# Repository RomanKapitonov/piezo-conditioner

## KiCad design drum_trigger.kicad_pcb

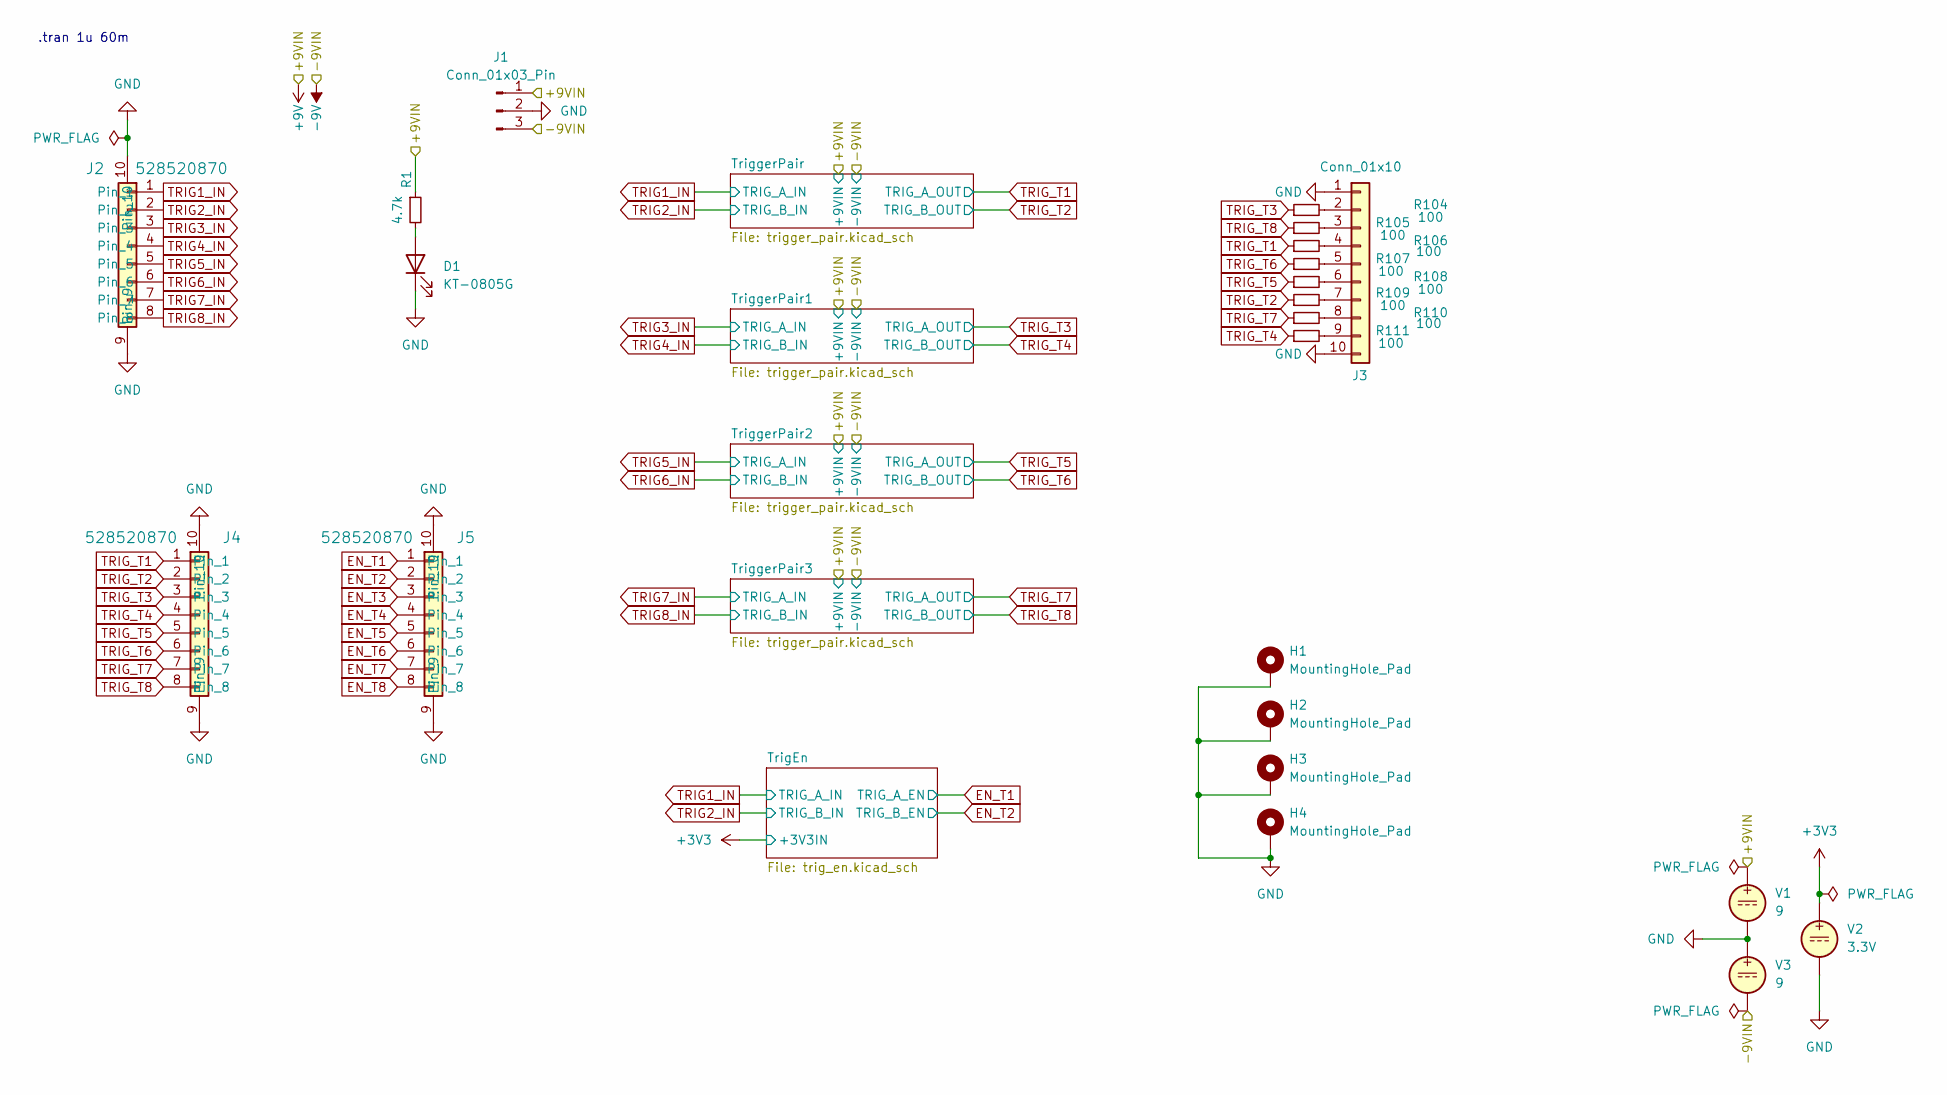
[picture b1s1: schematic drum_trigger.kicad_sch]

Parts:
D1: KT-0805G; LED_0805_2012Metric; LCSC C2297
H1, H2, H3, H4: MountingHole_Pad; MountingHole_2.2mm_M2_Pad_Via
J1: Conn_01x03_Pin; JST_PH_B3B-PH-K_1x03_P2.00mm_Vertical
J2, J4, J5: 528520870; CONN_MOLEX_528520870
J3: Conn_01x10; JST_ZH_B10B-ZR_1x10_P1.50mm_Vertical
R1: 4.7k; R_0603_1608Metric; LCSC C23162
R104, R105, R106, R107, R108, R109, R110, R111: 100; R_0402_1005Metric; LCSC C25076
V1, V3: 9
V2: 3.3V

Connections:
+9V: J1.1, R1.1, V1.1; also elsewhere on the board
-9V: J1.3, V3.2; also elsewhere on the board
GND: D1.1 (K), H1.1, H2.1, H3.1, H4.1, J1.2, J2.9, J2.10, J3.1, J3.10, J4.9, J4.10, J5.9, J5.10, V1.2, V2.2, V3.1; also elsewhere on the board
unnamed: D1.2 (A), R1.2
unnamed: J3.2, R104.2
unnamed: J3.3, R105.2
unnamed: J3.4, R106.2
unnamed: J3.5, R107.2
unnamed: J3.6, R108.2
unnamed: J3.7, R109.2
unnamed: J3.8, R110.2
unnamed: J3.9, R111.2
TRIG_T1: J4.1, R106.1; also elsewhere on the board
TRIG_T2: J4.2, R109.1; also elsewhere on the board
TRIG_T3: J4.3, R104.1; also elsewhere on the board
TRIG_T4: J4.4, R111.1; also elsewhere on the board
TRIG_T5: J4.5, R108.1; also elsewhere on the board
TRIG_T6: J4.6, R107.1; also elsewhere on the board
TRIG_T7: J4.7, R110.1; also elsewhere on the board
TRIG_T8: J4.8, R105.1; also elsewhere on the board

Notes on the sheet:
.tran 1u 60m

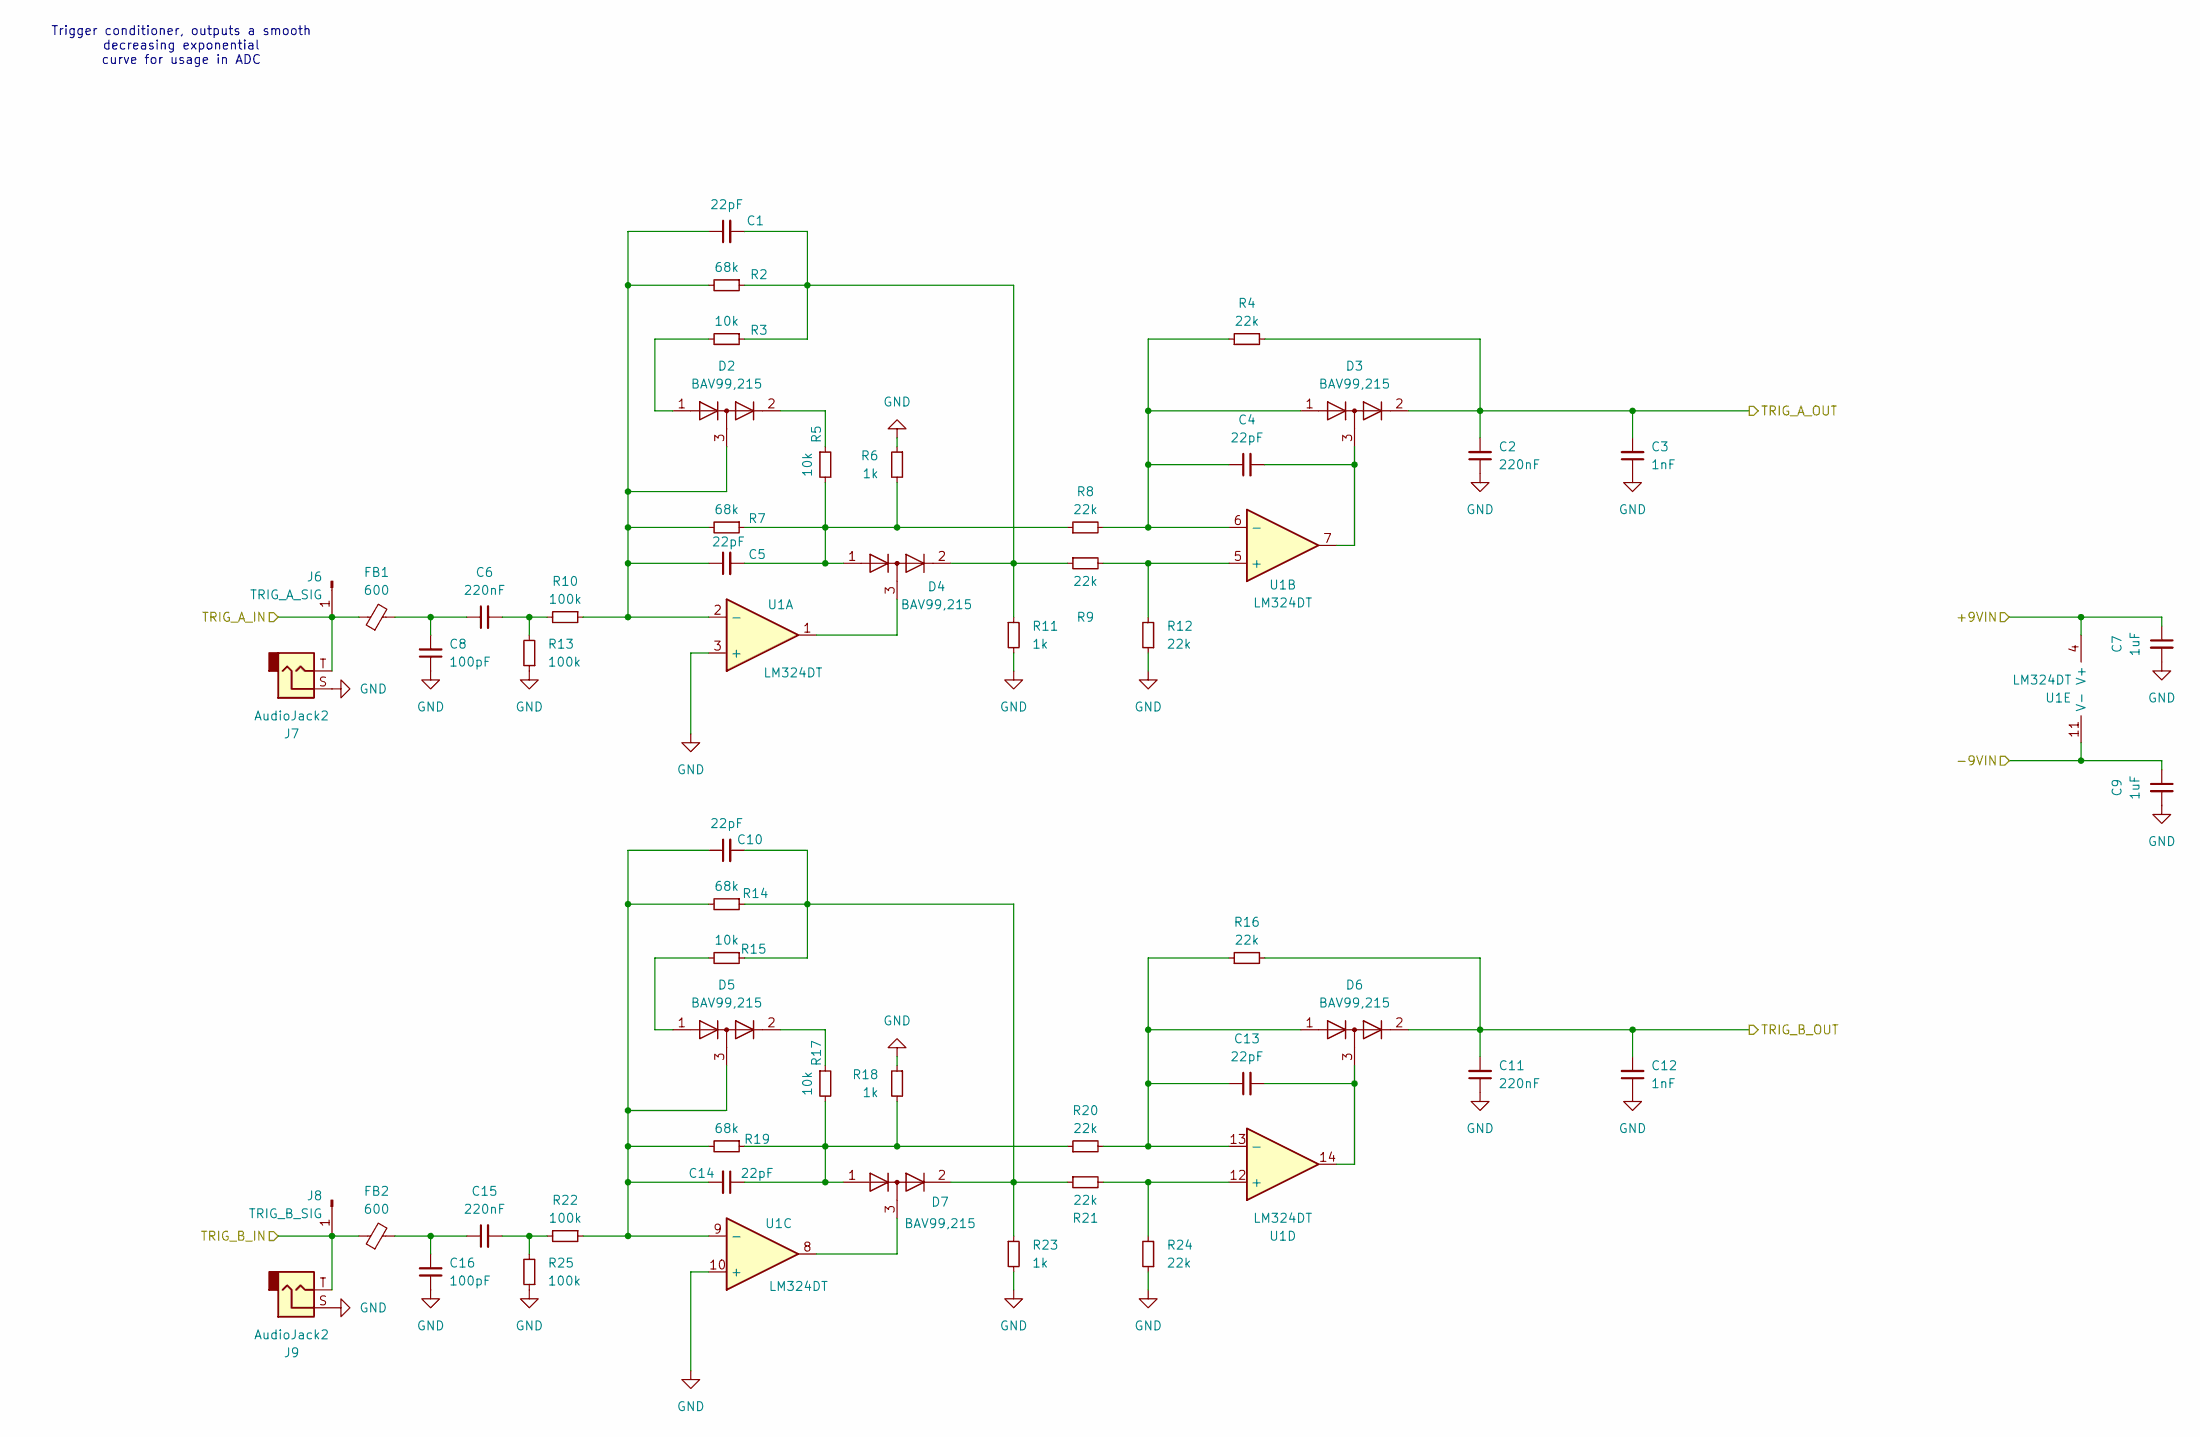
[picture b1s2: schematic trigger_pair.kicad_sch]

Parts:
C1, C4, C5, C10, C13, C14: 22pF; C_0402_1005Metric; LCSC C1555
C2, C6, C11, C15: 220nF; C_0603_1608Metric; LCSC C21120
C3, C12: 1nF; C_0603_1608Metric; LCSC C1588
C7, C9: 1uF; C_0603_1608Metric; LCSC C15849
C8, C16: 100pF; C_0603_1608Metric; LCSC C14858
D2, D3, D4, D5, D6, D7: BAV99,215; SOT-23; LCSC C2500
FB1, FB2: 600; L_0805_2012Metric; LCSC C1017
J6: TRIG_A_SIG
J7, J9: AudioJack2; Jack_6.35mm_Neutrik_NMJ4HFD2_Horizontal
J8: TRIG_B_SIG
R2, R7, R14, R19: 68k; R_0603_1608Metric; LCSC C23231
R3, R5, R15, R17: 10k; R_0402_1005Metric; LCSC C25744
R4, R8, R9, R12, R16, R20, R21, R24: 22k; R_0402_1005Metric; LCSC C25768
R6, R11, R18, R23: 1k; R_0402_1005Metric; LCSC C11702
R10, R13, R22, R25: 100k; R_0603_1608Metric; LCSC C25803
U1: LM324DT; SOIC-14_3.9x8.7mm_P1.27mm; LCSC C71035

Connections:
+9V: C7.1, U1.4 (V+); also elsewhere on the board
-9V: C9.1, U1.11 (V-); also elsewhere on the board
GND: C2.1, C3.1, C7.2, C8.1, C9.2, C11.1, C12.1, C16.1, J7.S, J9.S, R6.1, R11.2, R12.1, R13.1, R18.1, R23.2, R24.1, R25.1, U1.3 (+), U1.10 (+); also elsewhere on the board
unnamed: C4.2, D3.3 (K), U1.7
unnamed: C5.2, D4.1 (K), R5.2, R6.2, R7.1, R8.1
unnamed: C6.1, C8.2, FB1.2
unnamed: C6.2, R10.2, R13.2
unnamed: C13.2, D6.3 (K), U1.14
unnamed: C14.1, D7.1 (K), R17.2, R18.2, R19.1, R20.1
unnamed: C15.1, C16.2, FB2.2
unnamed: C15.2, R22.2, R25.2
unnamed: D2.2 (A), R5.1
unnamed: D2.1 (K), R3.2
unnamed: C1.2, D4.2 (A), R2.1, R3.1, R9.1, R11.1
unnamed: D4.3 (K), U1.1
unnamed: D5.2 (A), R17.1
unnamed: D5.1 (K), R15.2
unnamed: C10.2, D7.2 (A), R14.1, R15.1, R21.1, R23.1
unnamed: D7.3 (K), U1.8
unnamed: C1.1, C5.1, D2.3 (K), R2.2, R7.2, R10.1, U1.2 (-)
unnamed: R9.2, R12.2, U1.5 (+)
unnamed: C4.1, D3.1 (K), R4.1, R8.2, U1.6 (-)
unnamed: C10.1, C14.2, D5.3 (K), R14.2, R19.2, R22.1, U1.9 (-)
unnamed: R21.2, R24.2, U1.12 (+)
unnamed: C13.1, D6.1 (K), R16.1, R20.2, U1.13 (-)
TRIG1_IN: FB1.1, J7.T
TRIG2_IN: FB2.1, J9.T
TRIG_T1: C2.2, C3.2, D3.2 (A), R4.2; also elsewhere on the board
TRIG_T2: C11.2, C12.2, D6.2 (A), R16.2; also elsewhere on the board

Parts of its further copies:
C22, C25, C26, C31, C34, C35, C38, C41, C42, C47, C50, C51, C54, C57, C58, C63, C66, C67: 22pF; C_0402_1005Metric; LCSC C1555
C23, C27, C32, C36, C39, C43, C48, C52, C55, C59, C64, C68: 220nF; C_0603_1608Metric; LCSC C21120
C24, C33, C40, C49, C56, C65: 1nF; C_0603_1608Metric; LCSC C1588
C28, C30, C44, C46, C60, C62: 1uF; C_0603_1608Metric; LCSC C15849
C29, C37, C45, C53, C61, C69: 100pF; C_0603_1608Metric; LCSC C14858
D10, D11, D12, D13, D14, D15, D16, D17, D18, D19, D20, D21, D22, D23, D24, D25, D26, D27: BAV99,215; SOT-23; LCSC C2500
FB3, FB4, FB5, FB6, FB7, FB8: 600; L_0805_2012Metric; LCSC C1017
J11, J13, J15, J17, J19, J21: AudioJack2; Jack_6.35mm_Neutrik_NMJ4HFD2_Horizontal
R32, R37, R44, R49, R56, R61, R68, R73, R80, R85, R92, R97: 68k; R_0603_1608Metric; LCSC C23231
R33, R35, R45, R47, R57, R59, R69, R71, R81, R83, R93, R95: 10k; R_0402_1005Metric; LCSC C25744
R34, R38, R39, R42, R46, R50, R51, R54, R58, R62, R63, R66, R70, R74, R75, R78, R82, R86, R87, R90, R94, R98, R99, R102: 22k; R_0402_1005Metric; LCSC C25768
R36, R41, R48, R53, R60, R65, R72, R77, R84, R89, R96, R101: 1k; R_0402_1005Metric; LCSC C11702
R40, R43, R52, R55, R64, R67, R76, R79, R88, R91, R100, R103: 100k; R_0603_1608Metric; LCSC C25803
U3, U4, U5: LM324DT; SOIC-14_3.9x8.7mm_P1.27mm; LCSC C71035

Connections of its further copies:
+9V: C28.1, C44.1, C60.1, U3.4 (V+), U4.4 (V+), U5.4 (V+); also elsewhere on the board
-9V: C30.1, C46.1, C62.1, U3.11 (V-), U4.11 (V-), U5.11 (V-); also elsewhere on the board
GND: C23.1, C24.1, C28.2, C29.1, C30.2, C32.1, C33.1, C37.1, C39.1, C40.1, C44.2, C45.1, C46.2, C48.1, C49.1, C53.1, C55.1, C56.1, C60.2, C61.1, C62.2, C64.1, C65.1, C69.1, J11.S, J13.S, J15.S, J17.S, J19.S, J21.S, R36.1, R41.2, R42.1, R43.1, R48.1, R53.2, R54.1, R55.1, R60.1, R65.2, R66.1, R67.1, R72.1, R77.2, R78.1, R79.1, R84.1, R89.2, R90.1, R91.1, R96.1, R101.2, R102.1, R103.1, U3.3 (+), U3.10 (+), U4.3 (+), U4.10 (+), U5.3 (+), U5.10 (+); also elsewhere on the board
unnamed: C25.2, D11.3 (K), U3.7
unnamed: C26.2, D12.1 (K), R35.2, R36.2, R37.1, R38.1
unnamed: C27.1, C29.2, FB3.2
unnamed: C27.2, R40.2, R43.2
unnamed: C34.2, D14.3 (K), U3.14
unnamed: C35.1, D15.1 (K), R47.2, R48.2, R49.1, R50.1
unnamed: C36.1, C37.2, FB4.2
unnamed: C36.2, R52.2, R55.2
unnamed: C41.2, D17.3 (K), U4.7
unnamed: C42.2, D18.1 (K), R59.2, R60.2, R61.1, R62.1
unnamed: C43.1, C45.2, FB5.2
unnamed: C43.2, R64.2, R67.2
unnamed: C50.2, D20.3 (K), U4.14
unnamed: C51.1, D21.1 (K), R71.2, R72.2, R73.1, R74.1
unnamed: C52.1, C53.2, FB6.2
unnamed: C52.2, R76.2, R79.2
unnamed: C57.2, D23.3 (K), U5.7
unnamed: C58.2, D24.1 (K), R83.2, R84.2, R85.1, R86.1
unnamed: C59.1, C61.2, FB7.2
unnamed: C59.2, R88.2, R91.2
unnamed: C66.2, D26.3 (K), U5.14
unnamed: C67.1, D27.1 (K), R95.2, R96.2, R97.1, R98.1
unnamed: C68.1, C69.2, FB8.2
unnamed: C68.2, R100.2, R103.2
unnamed: D10.2 (A), R35.1
unnamed: D10.1 (K), R33.2
unnamed: C22.2, D12.2 (A), R32.1, R33.1, R39.1, R41.1
unnamed: D12.3 (K), U3.1
unnamed: D13.2 (A), R47.1
unnamed: D13.1 (K), R45.2
unnamed: C31.2, D15.2 (A), R44.1, R45.1, R51.1, R53.1
unnamed: D15.3 (K), U3.8
unnamed: D16.2 (A), R59.1
unnamed: D16.1 (K), R57.2
unnamed: C38.2, D18.2 (A), R56.1, R57.1, R63.1, R65.1
unnamed: D18.3 (K), U4.1
unnamed: D19.2 (A), R71.1
unnamed: D19.1 (K), R69.2
unnamed: C47.2, D21.2 (A), R68.1, R69.1, R75.1, R77.1
unnamed: D21.3 (K), U4.8
unnamed: D22.2 (A), R83.1
unnamed: D22.1 (K), R81.2
unnamed: C54.2, D24.2 (A), R80.1, R81.1, R87.1, R89.1
unnamed: D24.3 (K), U5.1
unnamed: D25.2 (A), R95.1
unnamed: D25.1 (K), R93.2
unnamed: C63.2, D27.2 (A), R92.1, R93.1, R99.1, R101.1
unnamed: D27.3 (K), U5.8
unnamed: C22.1, C26.1, D10.3 (K), R32.2, R37.2, R40.1, U3.2 (-)
unnamed: R39.2, R42.2, U3.5 (+)
unnamed: C25.1, D11.1 (K), R34.1, R38.2, U3.6 (-)
unnamed: C31.1, C35.2, D13.3 (K), R44.2, R49.2, R52.1, U3.9 (-)
unnamed: R51.2, R54.2, U3.12 (+)
unnamed: C34.1, D14.1 (K), R46.1, R50.2, U3.13 (-)
unnamed: C38.1, C42.1, D16.3 (K), R56.2, R61.2, R64.1, U4.2 (-)
unnamed: R63.2, R66.2, U4.5 (+)
unnamed: C41.1, D17.1 (K), R58.1, R62.2, U4.6 (-)
unnamed: C47.1, C51.2, D19.3 (K), R68.2, R73.2, R76.1, U4.9 (-)
unnamed: R75.2, R78.2, U4.12 (+)
unnamed: C50.1, D20.1 (K), R70.1, R74.2, U4.13 (-)
unnamed: C54.1, C58.1, D22.3 (K), R80.2, R85.2, R88.1, U5.2 (-)
unnamed: R87.2, R90.2, U5.5 (+)
unnamed: C57.1, D23.1 (K), R82.1, R86.2, U5.6 (-)
unnamed: C63.1, C67.2, D25.3 (K), R92.2, R97.2, R100.1, U5.9 (-)
unnamed: R99.2, R102.2, U5.12 (+)
unnamed: C66.1, D26.1 (K), R94.1, R98.2, U5.13 (-)
TRIG3_IN: FB3.1, J11.T
TRIG4_IN: FB4.1, J13.T
TRIG5_IN: FB5.1, J15.T
TRIG6_IN: FB6.1, J17.T
TRIG7_IN: FB7.1, J19.T
TRIG8_IN: FB8.1, J21.T
TRIG_T3: C23.2, C24.2, D11.2 (A), R34.2; also elsewhere on the board
TRIG_T4: C32.2, C33.2, D14.2 (A), R46.2; also elsewhere on the board
TRIG_T5: C39.2, C40.2, D17.2 (A), R58.2; also elsewhere on the board
TRIG_T6: C48.2, C49.2, D20.2 (A), R70.2; also elsewhere on the board
TRIG_T7: C55.2, C56.2, D23.2 (A), R82.2; also elsewhere on the board
TRIG_T8: C64.2, C65.2, D26.2 (A), R94.2; also elsewhere on the board

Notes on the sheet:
Trigger conditioner, outputs a smooth decreasing exponential curve for usage in ADC

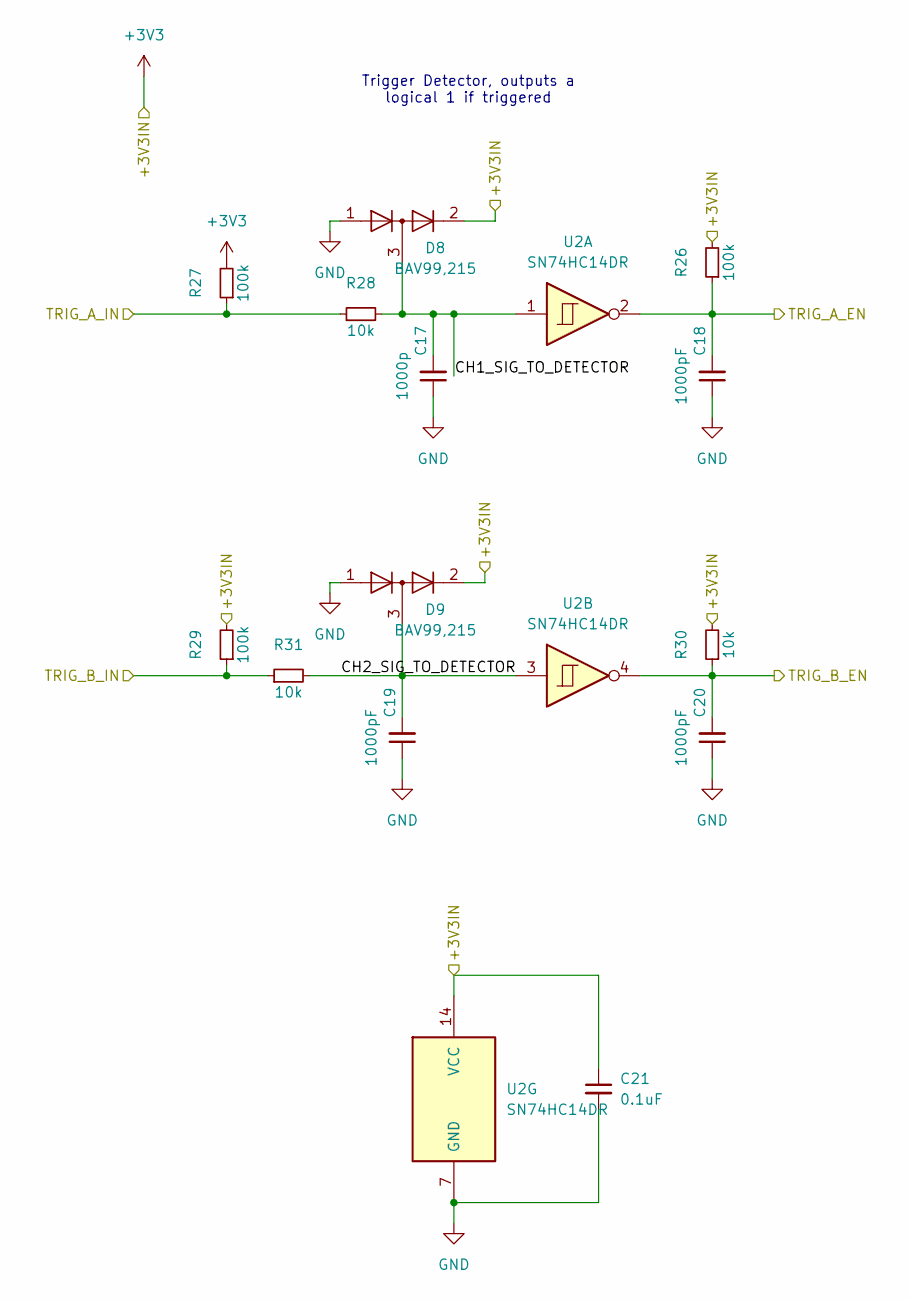
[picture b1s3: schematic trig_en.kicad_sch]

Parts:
C17: 1000p; C_0402_1005Metric
C18, C19, C20: 1000pF; C_0402_1005Metric
C21: 0.1uF; C_0402_1005Metric
D8, D9: BAV99,215; SOT-23; LCSC C2500
R26, R27, R29: 100k; R_0402_1005Metric
R28, R30, R31: 10k; R_0402_1005Metric
U2: SN74HC14DR; HEX_SCHMITT_SN74HC14DR

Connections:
unnamed: C17.1, C18.1, C19.1, C20.1, C21.2, D8.1 (K), D9.1 (K), U2.7 (GND)
unnamed: C17.2, D8.3 (K), R28.2, U2.1
unnamed: C18.2, R26.1, U2.2
unnamed: C19.2, D9.3 (K), R31.2, U2.3
unnamed: C20.2, R30.1, U2.4
unnamed: C21.1, D8.2 (A), D9.2 (A), R26.2, R27.2, R29.2, R30.2, U2.14 (VCC)
unnamed: R27.1, R28.1
unnamed: R29.1, R31.1

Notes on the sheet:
Trigger Detector, outputs a logical 1 if triggered

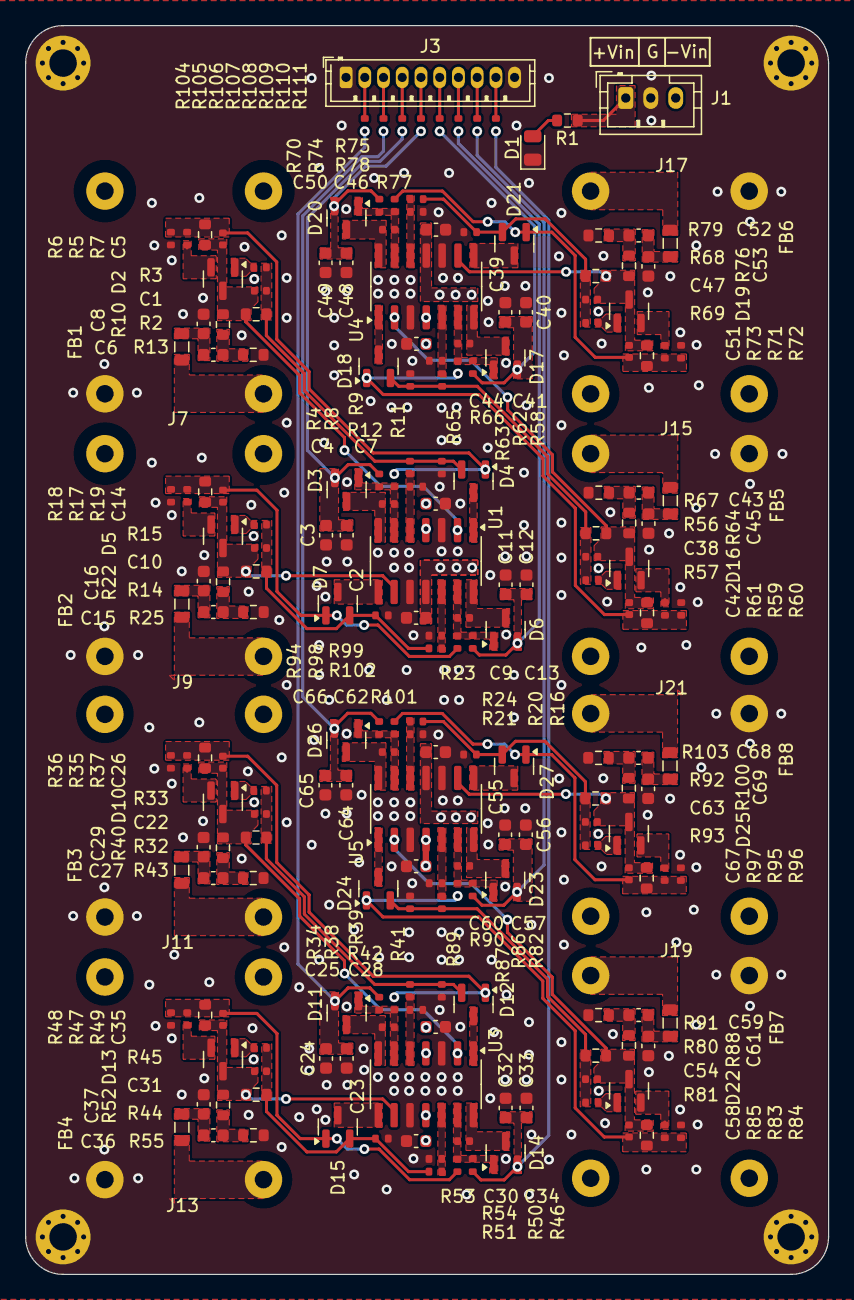
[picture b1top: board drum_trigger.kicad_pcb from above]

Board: 4 copper layers, 64.3 x 100.0 mm, 220 parts (0 on the bottom side), 116 nets.

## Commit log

2025-12-01 Test trigger circuit.
2025-12-01 Initial layout
2025-12-02 Double trigger layout to test
2025-12-02 Production ready pcb
2025-12-03 Minor upates to the pcb
2025-12-22 Add image to README
2026-02-23 Simulation fixes + board fixes
2026-03-01 Add channels
2026-03-02 Before instrumentation refactor
